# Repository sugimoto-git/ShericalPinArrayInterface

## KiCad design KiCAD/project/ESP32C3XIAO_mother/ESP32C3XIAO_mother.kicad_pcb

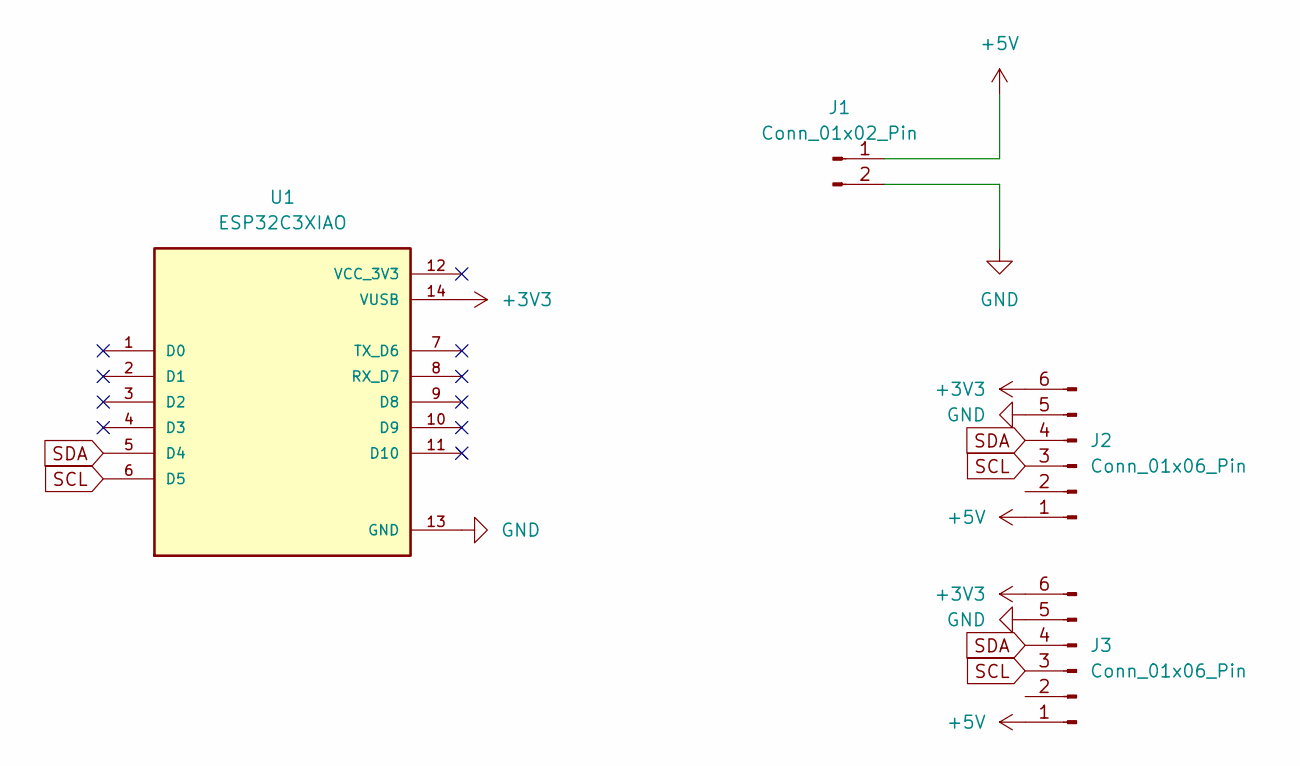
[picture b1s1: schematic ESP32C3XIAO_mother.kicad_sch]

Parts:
J1: Conn_01x02_Pin; PinHeader_1x02_P2.54mm_Vertical
J2, J3: Conn_01x06_Pin; PinHeader_1x06_P2.54mm_Vertical
U1: ESP32C3XIAO; PARTREV 23/05/2022

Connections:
+3V3: J2.6, J3.6, U1.14 (VUSB)
+5V: J1.1, J2.1, J3.1
GND: J1.2, J2.5, J3.5, U1.13 (GND)
SCL: J2.3, J3.3, U1.6 (D5)
SDA: J2.4, J3.4, U1.5 (D4)

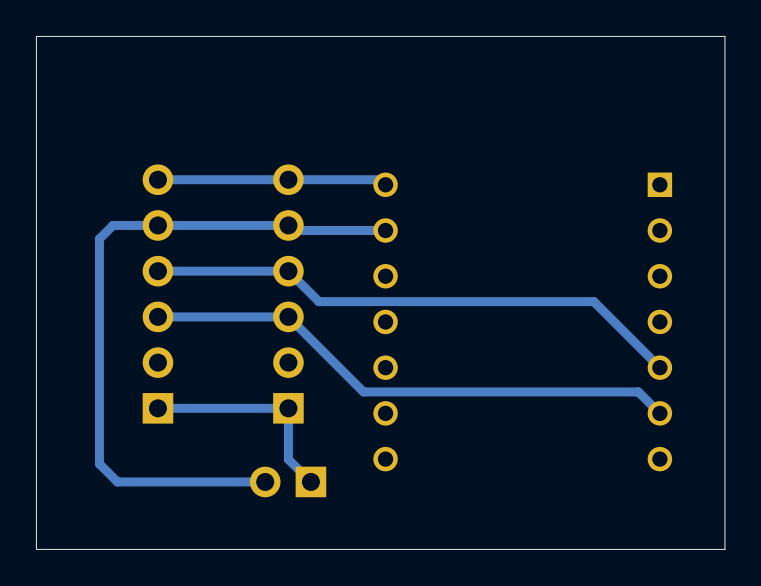
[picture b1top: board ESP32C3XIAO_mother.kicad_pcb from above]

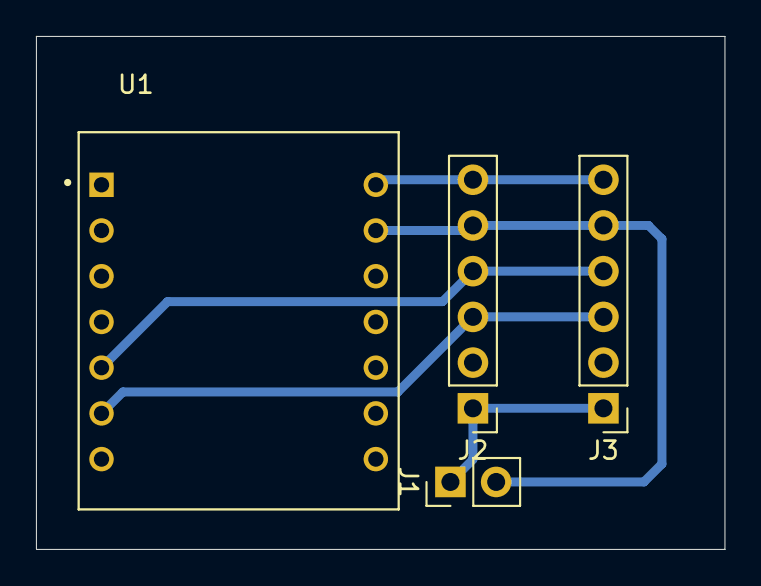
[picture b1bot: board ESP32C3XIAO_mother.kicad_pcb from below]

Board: 2 copper layers, 38.2 x 28.5 mm, 4 parts (4 on the bottom side), 5 nets.

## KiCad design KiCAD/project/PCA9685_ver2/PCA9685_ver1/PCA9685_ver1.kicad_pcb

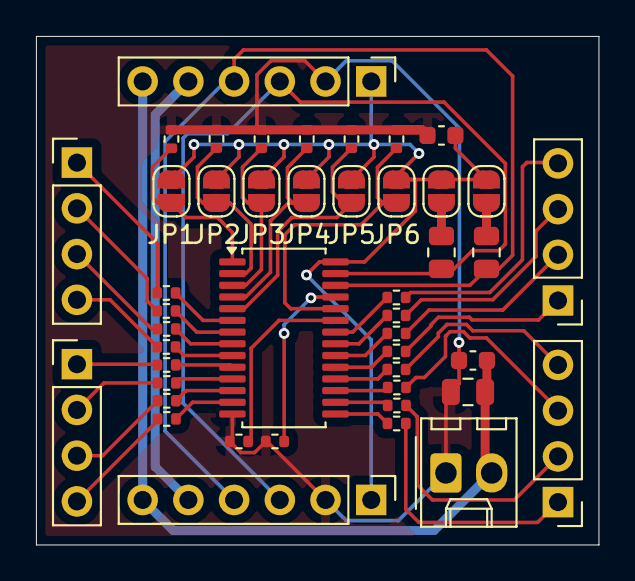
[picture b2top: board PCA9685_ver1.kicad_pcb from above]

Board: 2 copper layers, 31.2 x 28.2 mm, 45 parts (0 on the bottom side), 48 nets.

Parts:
C1, C3: 10μF; C_0603_1608Metric
C2: 47μF; C_0805_2012Metric
J1, J6, J7, J8: Conn_01x04_Pin; PinHeader_1x04_P2.54mm_Vertical
J2, J3: Conn_01x06_Pin; PinHeader_1x06_P2.54mm_Vertical
J4: Conn_01x02; Molex_KK-254_AE-6410-02A_1x02_P2.54mm_Vertical
JP1, JP2, JP3, JP4, JP5, JP6, JP7, JP8: SolderJumper_2_Open; SolderJumper-2_P1.3mm_Open_RoundedPad1.0x1.5mm
R1, R2, R19, R20, R21, R22, R23, R24: 10kΩ; R_0402_1005Metric
R3, R4, R5, R6, R7, R8, R9, R10, R11, R12, R13, R14, R15, R16, R17, R18: 220Ω; R_0402_1005Metric
R25, R26: 4.7kΩ; R_0805_2012Metric
U1: PCA9685; TSSOP-28_4.4x9.7mm_P0.65mm

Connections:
+3V3: C1.1, J2.1, J3.1, JP1.1 (A), JP2.1 (A), JP3.1 (A), JP4.1 (A), JP5.1 (A), JP6.1 (A), JP7.1 (A), JP8.2 (B), U1.28 (VDD)
+5V: C2.1, C3.1, J2.6, J3.6, J4.2
A0: JP1.2 (B), R19.2, U1.1 (A0)
A1: JP2.2 (B), R20.2, U1.2 (A1)
A2: JP3.2 (B), R21.2, U1.3 (A2)
A3: JP4.2 (B), R22.2, U1.4 (A3)
A4: JP5.2 (B), R23.2, U1.5 (A4)
A5: JP6.2 (B), R24.2, U1.24 (A5)
GND: C1.2, C2.2, C3.2, J2.2, J3.2, J4.1, R1.2, R2.2, R19.1, R20.1, R21.1, R22.1, R23.1, R24.1, U1.14 (GND)
unnamed: J1.1, R3.2
unnamed: J1.2, R4.2
unnamed: J1.3, R5.2
unnamed: J1.4, R6.2
unnamed: J6.1, R7.2
unnamed: J6.2, R8.2
unnamed: J6.3, R9.2
unnamed: J6.4, R10.2
unnamed: J7.1, R11.2
unnamed: J7.2, R12.2
unnamed: J7.3, R13.2
unnamed: J7.4, R14.2
unnamed: J8.1, R15.2
unnamed: J8.2, R16.2
unnamed: J8.3, R17.2
unnamed: J8.4, R18.2
unnamed: JP7.2 (B), R25.1
unnamed: JP8.1 (A), R26.1
unnamed: R1.1, U1.23 (#OE)
unnamed: R2.1, U1.25 (EXTCLK)
unnamed: R3.1, U1.6 (PWM0)
unnamed: R4.1, U1.7 (PWM1)
unnamed: R5.1, U1.8 (PWM2)
unnamed: R6.1, U1.9 (PWM3)
unnamed: R7.1, U1.10 (PWM4)
unnamed: R8.1, U1.11 (PWM5)
unnamed: R9.1, U1.12 (PWM6)
unnamed: R10.1, U1.13 (PWM7)
unnamed: R11.1, U1.15 (PWM8)
unnamed: R12.1, U1.16 (PWM9)
unnamed: R13.1, U1.17 (PWM10)
unnamed: R14.1, U1.18 (PWM11)
unnamed: R15.1, U1.19 (PWM12)
unnamed: R16.1, U1.20 (PWM13)
unnamed: R17.1, U1.21 (PWM14)
unnamed: R18.1, U1.22 (PWM15)
OE: J2.5, J3.5
SCL: J2.4, J3.4, R26.2, U1.26 (SCL)
SDA: J2.3, J3.3, R25.2, U1.27 (SDA)

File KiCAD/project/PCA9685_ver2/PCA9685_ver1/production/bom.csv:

Designator,Footprint,Quantity,Value,LCSC Part #
"C1, C3",0603,2,10μF,
C2,0805,1,47μF,
"J1, J6, J7, J8",PinHeader_1x04_P2.54mm_Vertical,4,Conn_01x04_Pin,
"J2, J3",PinHeader_1x06_P2.54mm_Vertical,2,Conn_01x06_Pin,
J4,Molex_KK-254_AE-6410-02A_1x02_P2.54mm_Vertical,1,Conn_01x02,
"R1, R19, R2, R20, R21, R22, R23, R24",0402,8,10kΩ,
"R10, R11, R12, R13, R14, R15, R16, R17, R18, R3, R4, R5, R6, R7, R8, R9",0402,16,220Ω,
"R25, R26",0805,2,4.7kΩ,
U1,TSSOP-28_4.4x9.7mm_P0.65mm,1,PCA9685,

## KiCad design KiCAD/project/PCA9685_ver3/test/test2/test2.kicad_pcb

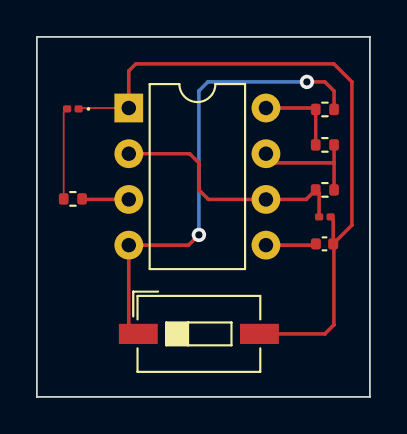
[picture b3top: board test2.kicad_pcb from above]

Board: 2 copper layers, 18.5 x 20.0 mm, 9 parts (0 on the bottom side), 8 nets.

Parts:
C1: 0.01u; C_0402_1005Metric
C2: 1u; C_0201_0603Metric
D1: LED; LED_0201_0603Metric
R1: 10k; R_0402_1005Metric
R2: 6.8k; R_0402_1005Metric
R3: 68k; R_0402_1005Metric
R4: 330; R_0402_1005Metric
SW1: SW_DPST_x2; SW_DIP_SPSTx01_Slide_6.7x4.1mm_W6.73mm_P2.54mm_LowProfile_J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
U1: NE555P; DIP-8_W7.62mm

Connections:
+5V: R1.1, R2.1, U1.8 (VCC)
GND: C1.2, C2.2, D1.1 (K), SW1.2 (B), U1.1 (GND)
unnamed: D1.2 (A), R4.2
unnamed: R1.2, SW1.1 (A), U1.4 (R)
unnamed: C1.1, U1.5 (CV)
unnamed: R2.2, R3.1, U1.7 (DIS)
unnamed: R4.1, U1.3 (Q)
unnamed: C2.1, R3.2, U1.2 (TR), U1.6 (THR)

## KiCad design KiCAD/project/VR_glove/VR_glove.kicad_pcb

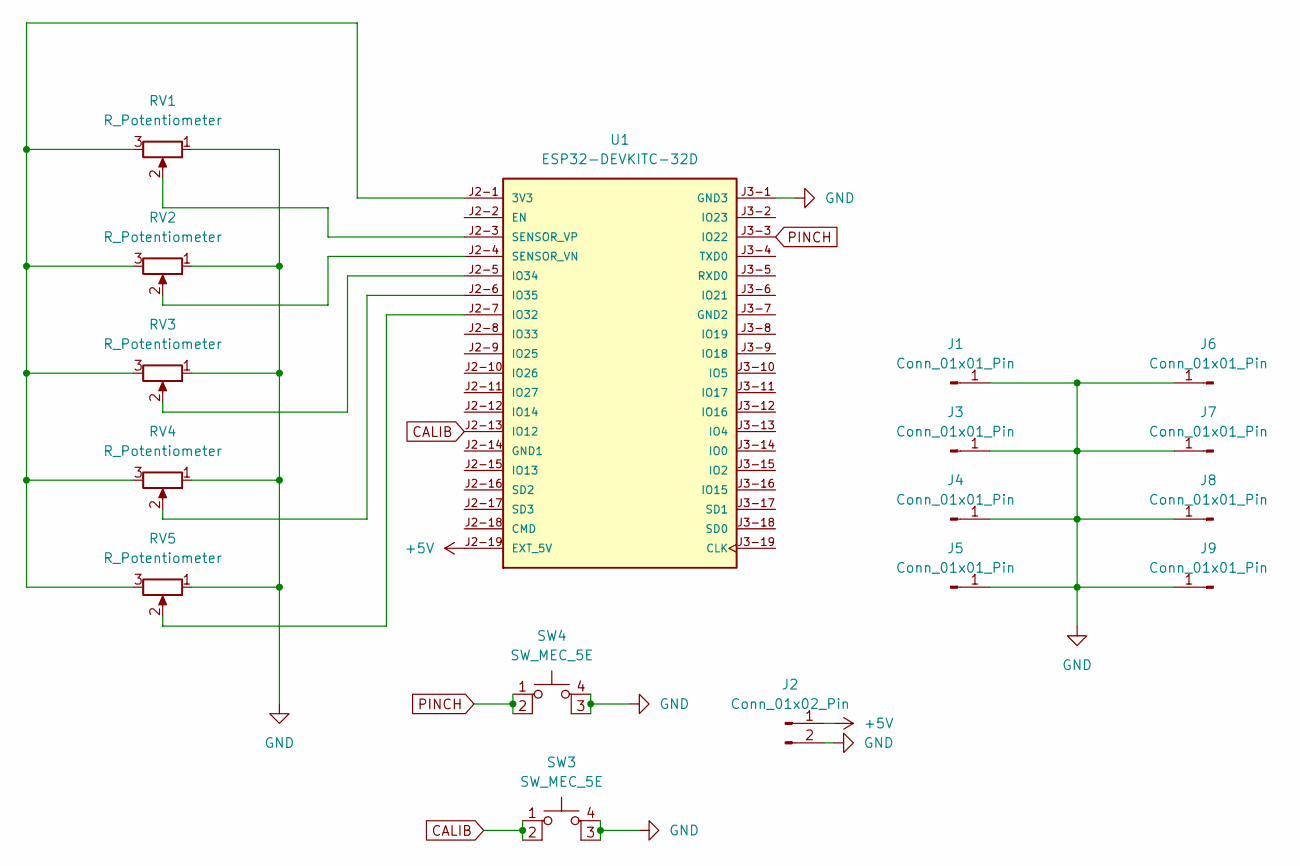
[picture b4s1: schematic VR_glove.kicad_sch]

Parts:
J1, J3, J4, J5, J6, J7, J8, J9: Conn_01x01_Pin; THR_pin1
J2: Conn_01x02_Pin; PinHeader_1x02_P2.54mm_Vertical
RV1, RV2, RV3, RV4, RV5: R_Potentiometer; Potentiometer_Alps_RK09Y11_Single_Horizontal
SW3, SW4: SW_MEC_5E; button_4pin
U1: ESP32-DEVKITC-32D; MODULE_ESP32-DEVKITC-32D; PARTREV V4

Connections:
+5V: J2.1, U1.J2-19 (EXT_5V)
CALIB: SW3.1, SW3.2, U1.J2-13 (IO12)
GND: J1.1, J2.2, J3.1, J4.1, J5.1, J6.1, J7.1, J8.1, J9.1, RV1.1, RV2.1, RV3.1, RV4.1, RV5.1, SW3.3 (K), SW3.4 (A), SW4.3 (K), SW4.4 (A), U1.J3-1 (GND3)
unnamed: RV1.3, RV2.3, RV3.3, RV4.3, RV5.3, U1.J2-1 (3V3)
unnamed: RV5.2, U1.J2-7 (IO32)
unnamed: RV3.2, U1.J2-5 (IO34)
unnamed: RV4.2, U1.J2-6 (IO35)
unnamed: RV2.2, U1.J2-4 (SENSOR_VN)
unnamed: RV1.2, U1.J2-3 (SENSOR_VP)
PINCH: SW4.1, SW4.2, U1.J3-3 (IO22)

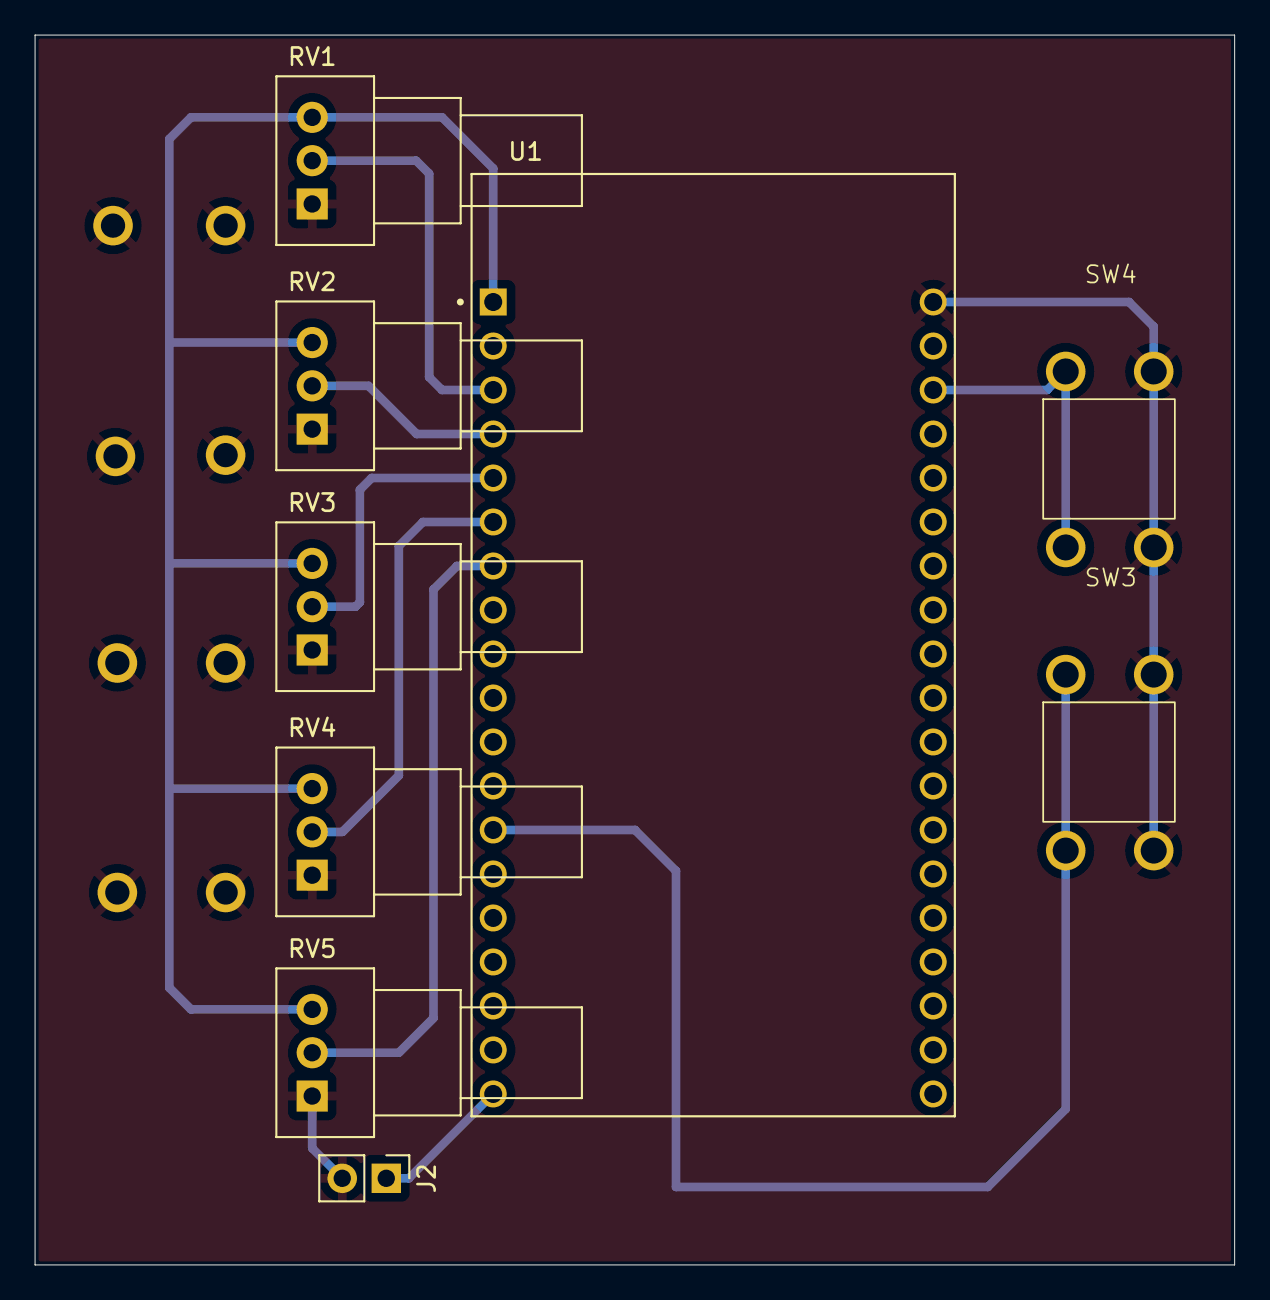
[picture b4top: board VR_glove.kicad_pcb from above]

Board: 2 copper layers, 69.2 x 71.0 mm, 17 parts (0 on the bottom side), 10 nets.
